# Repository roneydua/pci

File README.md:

<p align="center">
  
</p>

<h3 align="center">Placa controladora para quadricópteros</h3>

<div align="center">

<!--  -->
<!--  -->

</div>

---

<p align="center"> Projeto de placa controladora de código aberto para controle de VANTs.
    <br> 
</p>

## 📝 Indice

## 🧐 Sobre 

Write about 1-2 paragraphs describing the purpose of your project.

## 🏁 Getting Started 

<!-- These instructions will get you a copy of the project up and running on your local machine for development and testing purposes. See [deployment](#deployment) for notes on how to deploy the project on a live system. -->

### Pre-requisitos

<!-- What things you need to install the software and how to install them. -->
O projeto é desenvolvido com os softwares de código aberto FreeCAD e do KiCAD nas versões:
- FreeCAD
  ```
  OS: Debian GNU/Linux 11 (bullseye) (GNOME/gnome-xorg)
  Word size of FreeCAD: 64-bit
  Version: 0.20.25943 (Git) AppImage
  Build type: Release
  Branch: master
  Hash: a65464b722a846bd2999aa2fecdff1132b15b297
  Python version: 3.9.7
  Qt version: 5.12.9
  Coin version: 4.0.0
  OCC version: 7.5.2
  Locale: Portuguese/Brazil (pt_BR)```

- KiCad
  ```
  Application: KiCad
  Version: 5.1.10, release build
  Libraries:
  wxWidgets 3.0.5
  libcurl/7.71.1-DEV GnuTLS/3.6.15 (NSS/3.49.2) (OpenSSL/1.1.1k) zlib/1.2.11 libidn2/2.3.0
  Platform: Linux 5.10.0-9-amd64 x86_64, 64 bit, Little endian, wxGTK
  Build Info:
    wxWidgets: 3.0.5 (wchar_t,wx containers,compatible with 2.8) GTK+ 3.24
    Boost: 1.77.0
    OpenCASCADE Technology: 7.5.1
    Curl: 7.71.1-DEV
    Compiler: GCC 10.2.0 with C++ ABI 1014
  ```

## 🎈 Utilização 

Para utilizar basta clonar o repositório com o comando
```
  git clone https://github.com/roneydua/pci.git
```

## ✍️ Autor 

- [@roneydua](https://roneydua.github.io/) - Site pessoal

<!-- ## 🎉 Agradecimentos  -->

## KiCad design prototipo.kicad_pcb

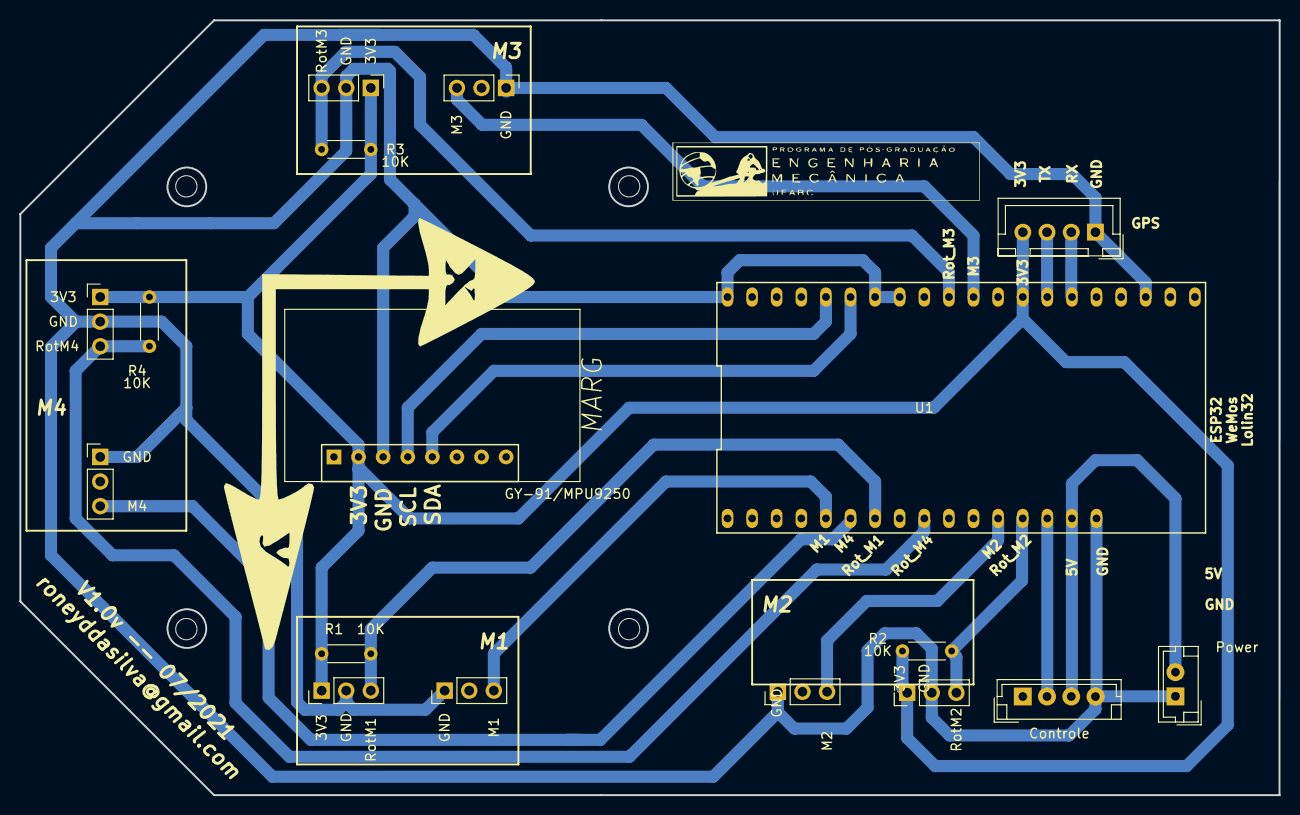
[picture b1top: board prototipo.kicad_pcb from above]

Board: 2 copper layers, 130.0 x 80.0 mm, 19 parts (0 on the bottom side), 16 nets.

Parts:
Controle: Controle; JST_EH_B04B-EH-A_04x2.50mm_Straight
GPS: GPS; JST_XH_B04B-XH-A_04x2.50mm_Straight
GY-91/MPU9250: MPU9250; mpu9250
M1: M1; PinHeader_1x03_P2.54mm_Vertical
M2: M2; PinHeader_1x03_P2.54mm_Vertical
M3: M3; PinHeader_1x03_P2.54mm_Vertical
M4: M4; PinHeader_1x03_P2.54mm_Vertical
Power: Power; JST_EH_B02B-EH-A_02x2.50mm_Straight
R1, R2, R3, R4: 10K; R_Axial_DIN0204_L3.6mm_D1.6mm_P5.08mm_Horizontal
RotM1: RotM1; PinHeader_1x03_P2.54mm_Vertical
RotM2: RotM2; PinHeader_1x03_P2.54mm_Vertical
RotM3: RotM3; PinHeader_1x03_P2.54mm_Vertical
RotM4: RotM4; PinHeader_1x03_P2.54mm_Vertical
U1: Lolin32; esp32_lolin32
U2: sistema_coordenadas; sistema_cordenadas
U4: posmec; logo_posmec

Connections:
3V: GPS.4, GY-91/MPU9250.2, R1.1, R2.1, R3.1, R4.1, RotM1.1, RotM2.1, RotM3.1, RotM4.1, U1.29
+5V: Controle.3, Power.2, U1.15
GND: Controle.4, GPS.1, GY-91/MPU9250.3, M1.1, M2.1, M3.1, M4.1, Power.1, RotM1.2, RotM2.2, RotM3.2, RotM4.2, U1.16, U1.17, U1.23, U1.24, U1.34
Rot_M1: R1.2, RotM1.3, U1.7
Rot_M2: R2.2, RotM2.3, U1.13
Rot_M3: R3.2, RotM3.3, U1.26
Rot_M4: R4.2, RotM4.3, U1.9
SCL: GY-91/MPU9250.4, U1.21
SDA: GY-91/MPU9250.5, U1.22
com_M1: M1.3, U1.5
com_M2: M2.3, U1.12
com_M3: M3.3, U1.27
com_M4: M4.3, U1.6
rx_cont: Controle.2, U1.14
rx_gps: GPS.2, U1.31
tx_gps: GPS.3, U1.30

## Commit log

2021-11-25 Primeiro envio
2021-11-25 Atualização docs
2021-11-25 esquema

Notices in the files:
README.md:
License: MIT
